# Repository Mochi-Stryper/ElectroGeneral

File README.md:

# ElectroGeneral
 General Repository

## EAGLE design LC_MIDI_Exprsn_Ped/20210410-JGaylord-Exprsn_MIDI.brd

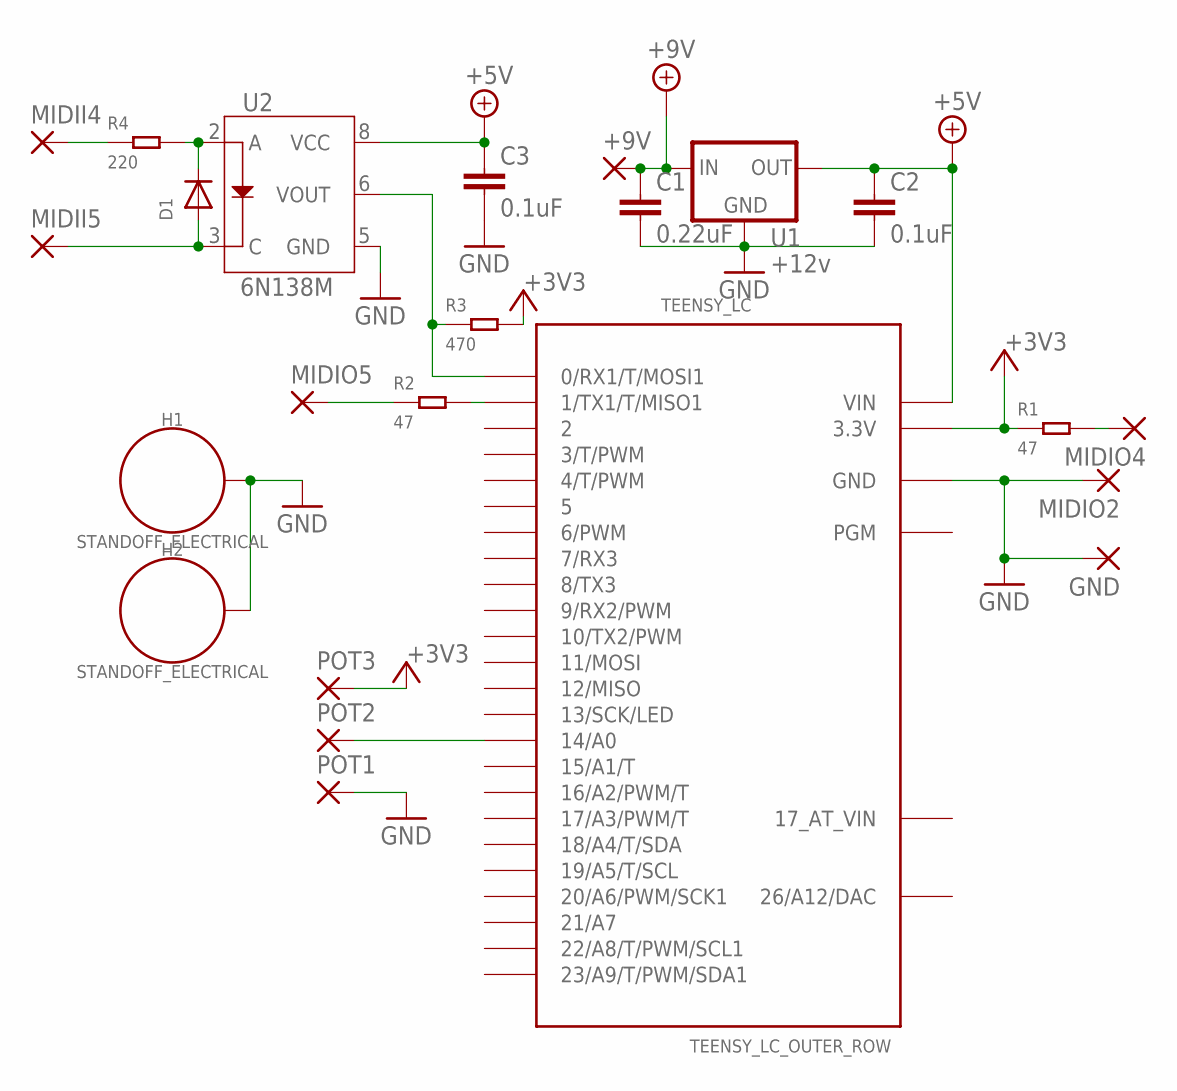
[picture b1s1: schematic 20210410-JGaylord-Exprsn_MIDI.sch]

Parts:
+9V: WIREPAD2,15/1,0; 2,15/1,0
C1: 0.22uF; 0603
C2, C3: 0.1uF; 0603
D1: DIODESOD-123; SOD-123
GND: WIREPAD2,15/1,0; 2,15/1,0
H1, H2: STANDOFF_ELECTRICAL; STANDOFF-ELECTRICAL
MIDII4, MIDII5: WIREPAD2,15/1,0; 2,15/1,0
MIDIO2, MIDIO4, MIDIO5: WIREPAD2,15/1,0; 2,15/1,0
POT1, POT2, POT3: WIREPAD2,15/1,0; 2,15/1,0
R1, R2: 47; R0805
R3: 470; R0805
R4: 220; R0805
TEENSY_LC: TEENSY_LC_OUTER_ROW; TEENSY_3.0-3.2&LC_OUTER_ROW
U1: +12v; TO-252
U2: 6N138M; 8-SMD

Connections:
26/A12/DAC: TEENSY_LC.RESET/DAC (26/A12/DAC)
+3V3: POT3.1, R1.1, R3.2, TEENSY_LC.3.3V, TEENSY_LC.3.3V1 (3.3V)
+5V: C2.1, C3.1, TEENSY_LC.VIN, U1.2 (OUT), U2.8 (VCC)
+9V: +9V.1, C1.1, U1.1 (IN)
GND: C1.2, C2.2, C3.2, GND.1, H1.P1, H2.P1, MIDIO2.1, POT1.1, TEENSY_LC.AGND (GND), TEENSY_LC.GND, TEENSY_LC.GND1 (GND), U1.3 (GND), U2.5 (GND)
unnamed: R2.2, TEENSY_LC.1 (1/TX1/T/MISO1)
unnamed: MIDIO5.1, R2.1
unnamed: POT2.1, TEENSY_LC.14/A0
unnamed: R3.1, TEENSY_LC.0 (0/RX1/T/MOSI1), U2.6 (VOUT)
unnamed: D1.C, R4.2, U2.2 (A)
unnamed: MIDIO4.1, R1.2
unnamed: D1.A, MIDII5.1, U2.3 (C)
unnamed: MIDII4.1, R4.1

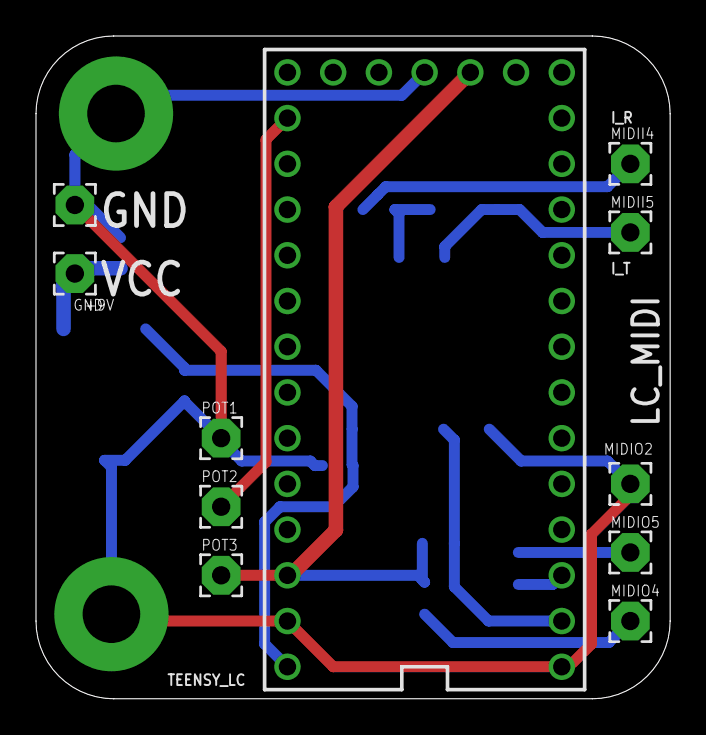
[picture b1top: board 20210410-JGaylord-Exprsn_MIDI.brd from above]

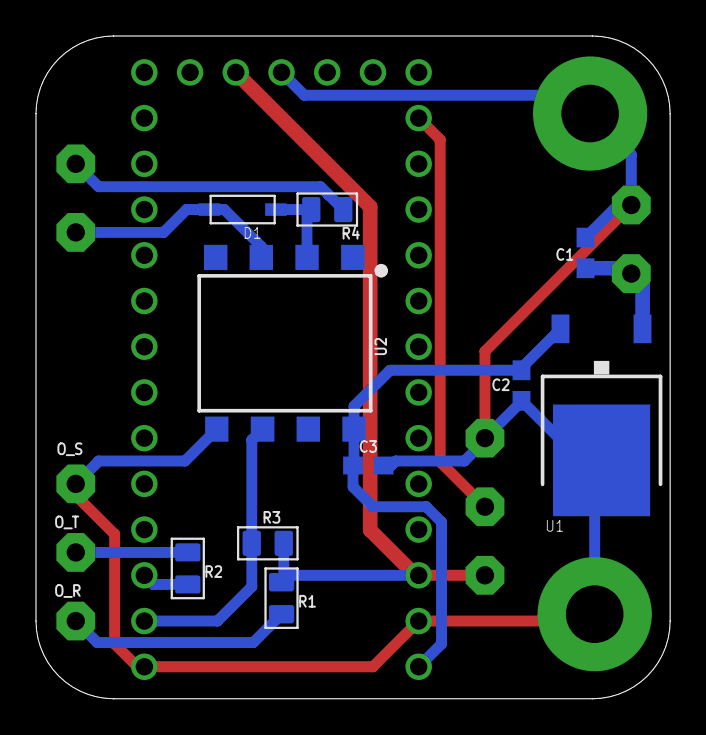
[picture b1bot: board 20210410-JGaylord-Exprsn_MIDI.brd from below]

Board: 2 copper layers, 35.2 x 36.8 mm, 23 parts (10 on the bottom side), 12 nets.

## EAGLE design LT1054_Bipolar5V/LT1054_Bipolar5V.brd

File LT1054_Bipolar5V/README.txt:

LT1054
Regulate 9V to 5V and -5V
The -5V regulator is notably overpowered for the LT1054 in terms of current draw. Implementing a lesser regulator with similar pinout may be a solution.
Attempting to draw more than ~100mA will generate a lot of heat from the LT1054.

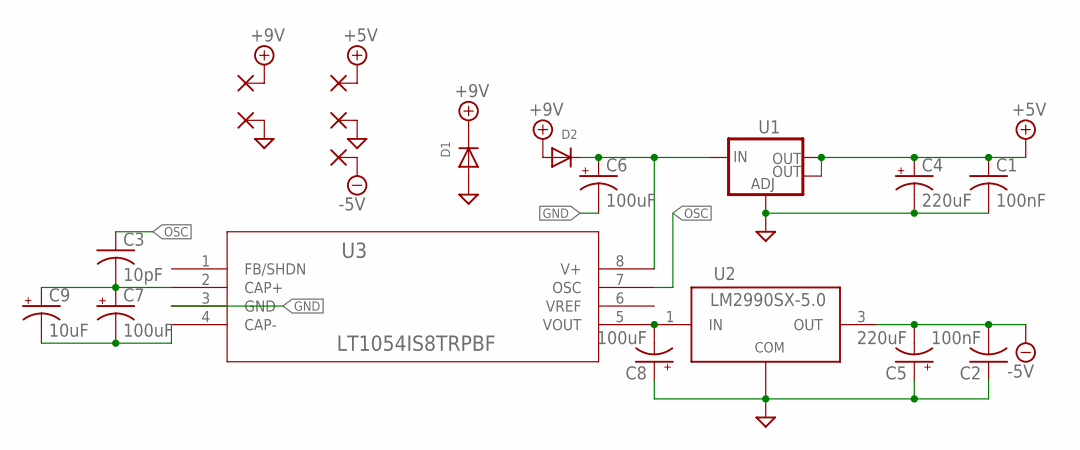
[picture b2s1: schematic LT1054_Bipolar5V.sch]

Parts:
C1, C2: 100nF; C0603
C3: 10pF; C0603
C4, C5: 220uF; PANASONIC_E
C6, C7, C8: 100uF; PANASONIC_D
C9: 10uF; PANASONIC_B
D1, D2: DIODESOD-123; SOD-123
PAD1: SMD2; SMD1,27-2,54
PAD2, PAD3, PAD4, PAD5: 1,6/0,8
U1: V_REG_LM1117SOT223; SOT223
U2: LM2990SX-5.0; D2PAK-3
U3: LT1054IS8TRPBF; SO-8_S

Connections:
+5V: C1.1, C4.+, PAD3.1, U1.2 (OUT), U1.4 (OUT)
+9V: D1.C, D2.A, PAD1.1
-5V: C2.2, C5.-, PAD5.1, U2.3 (OUT)
GND: C1.2, C2.1, C4.-, C5.+, C6.-, C8.+, D1.A, PAD2.1, PAD4.1, U1.1 (ADJ), U2.2 (COM), U2.4 (COM), U3.3 (GND)
unnamed: C6.+, D2.C, U1.3 (IN), U3.8 (V+)
unnamed: C8.-, U2.1 (IN), U3.5 (VOUT)
unnamed: C3.2, C7.+, C9.+, U3.2 (CAP+)
unnamed: C7.-, C9.-, U3.4 (CAP-)
OSC: C3.1, U3.7 (OSC)
VREF: U3.6 (VREF)

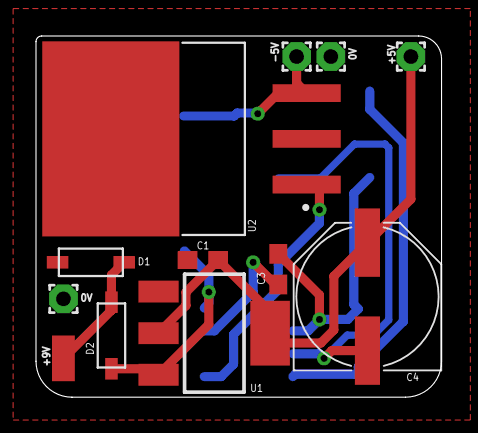
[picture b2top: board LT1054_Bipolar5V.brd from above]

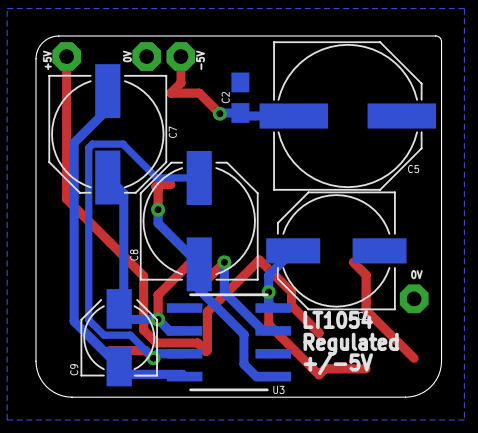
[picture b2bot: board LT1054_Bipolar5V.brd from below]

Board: 2 copper layers, 22.5 x 20.1 mm, 19 parts (7 on the bottom side), 9 nets.

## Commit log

2020-10-24 Added LT1054_Bipolar5V
    Added LT1054_Bipolar5V
2021-04-21 Added LC_MIDI_Exprsn
    Added LC_MIDI_Exprsn
2021-04-24 Added 4301S to DIP
    Added 4301S to DIP

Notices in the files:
parts and their libraries:
SparkFun-Capacitors: Licensing: Creative Commons ShareAlike 4.0 International - https://creativecommons.org/licenses/by-sa/4.0
